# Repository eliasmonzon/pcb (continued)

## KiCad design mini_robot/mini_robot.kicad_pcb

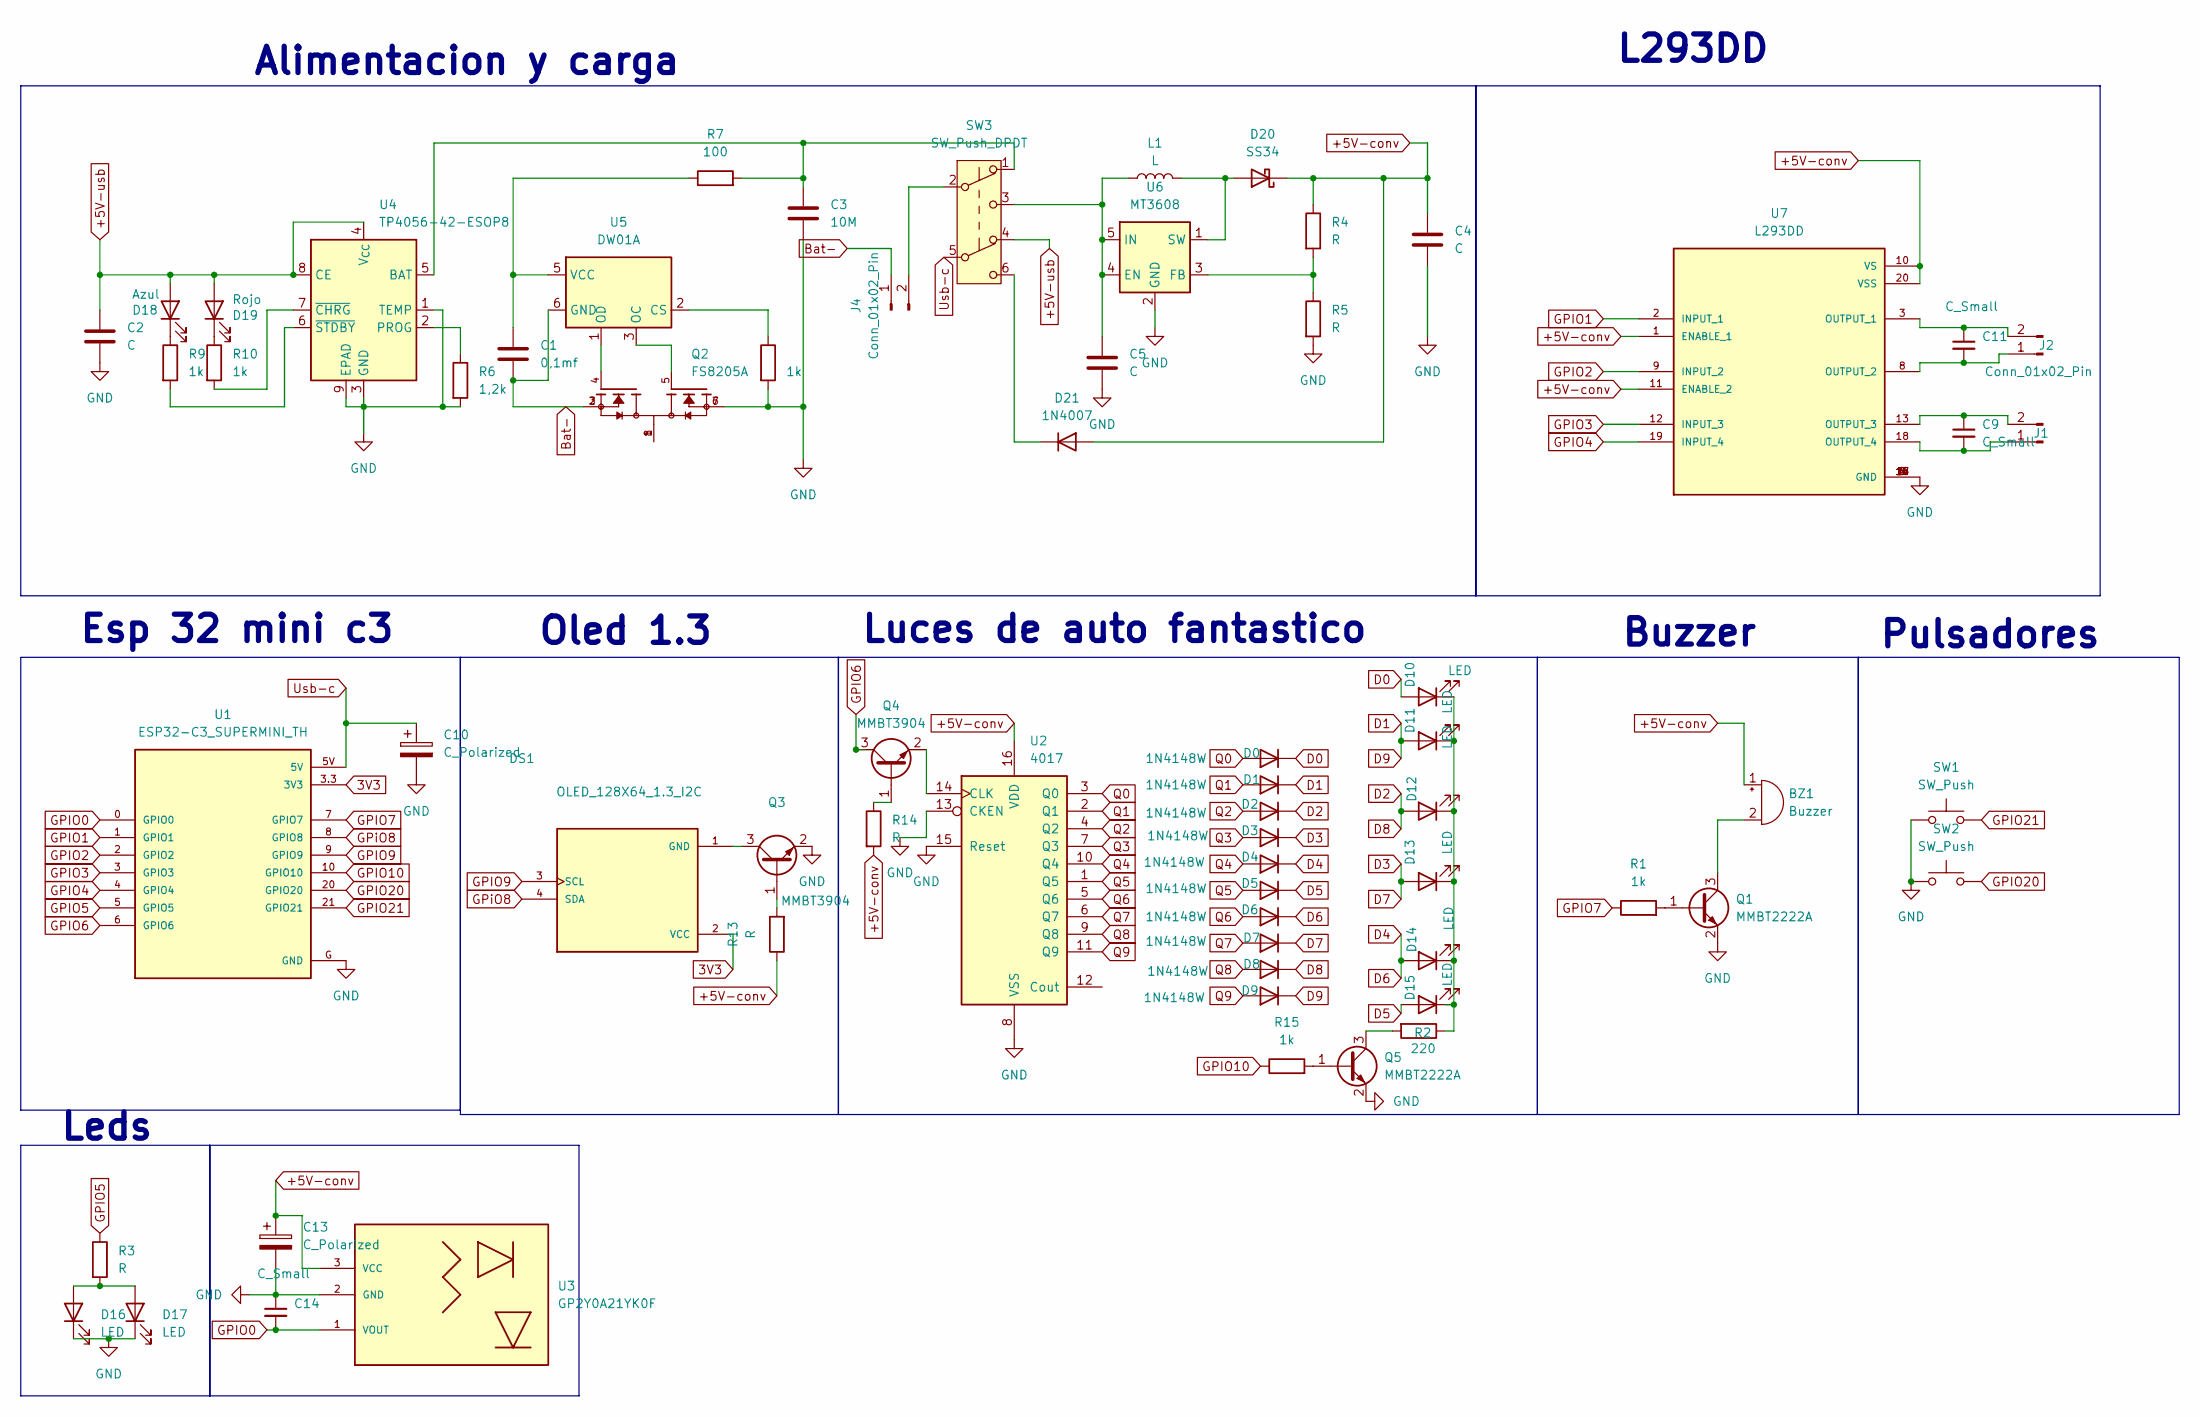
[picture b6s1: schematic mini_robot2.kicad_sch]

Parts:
BZ1: Buzzer; Buzzer_12x9.5RM7.6
C1: 0,1mf; C_1206_3216Metric
C2, C4, C5: C; C_1206_3216Metric
C3: 10M; C_1206_3216Metric
C9, C11, C14: C_Small; C_1206_3216Metric
C10, C13: C_Polarized; CP_Elec_3x5.3
D0, D1, D2, D3, D4, D5, D6, D7, D8, D9: 1N4148W; D_SOD-123
D10, D11, D12, D13, D14, D15, D16, D17: LED; LED_D5.0mm_Horizontal_O3.81mm_Z3.0mm
D18: Azul; LED_D3.0mm
D19: Rojo; LED_D3.0mm
D20: SS34; D_SMA
D21: 1N4007; D_1206_3216Metric_Pad1.42x1.75mm_HandSolder
DS1: OLED_128X64_1.3_I2C; LCD_OLED_128X64_1.3_I2C; PARTREV NA
J1, J2, J4: Conn_01x02_Pin; JST_EH_B2B-EH-A_1x02_P2.50mm_Vertical
L1: L; L_12x12mm_H8mm
Q1, Q5: MMBT2222A; SOT-23
Q2: FS8205A; SSO-8_6.8x5.9mm_P1.27mm_Clearance7mm; PARTREV 1.7
Q3, Q4: MMBT3904; SOT-23
R1, R8, R9, R10, R15: 1k; R_1206_3216Metric
R2: 220; R_1206_3216Metric
R3, R4, R5, R13, R14: R; R_1206_3216Metric
R6: 1,2k; R_1206_3216Metric
R7: 100; R_1206_3216Metric
SW1, SW2: SW_Push; SW_PUSH-12mm
SW3: SW_Push_DPDT; SW_E-Switch_EG2219_DPDT_Angled
U1: ESP32-C3_SUPERMINI_TH; MODULE_ESP32-C3_SUPERMINI_TH
U2: 4017; SOIC-16_3.9x9.9mm_P1.27mm
U3: GP2Y0A21YK0F; JST_EH_B3B-EH-A_1x03_P2.50mm_Vertical
U4: TP4056-42-ESOP8; SOIC-8-1EP_3.9x4.9mm_P1.27mm_EP2.41x3.3mm_ThermalVias
U5: DW01A; SOT-23-6
U6: MT3608; SOT-23-6
U7: L293DD; SOIC127P1032X265-20N; PARTREV N/A

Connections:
3V3: DS1.2 (VCC), U1.3.3 (3V3)
+5V-conv: BZ1.1 (+), C4.1, C13.1, D20.1 (K), D21.2 (A), R4.1, R13.1, R14.2, U2.16 (VDD), U3.3 (VCC), U7.1 (ENABLE_1), U7.10 (VS), U7.11 (ENABLE_2), U7.20 (VSS)
+5V-usb: C2.1, D18.2 (A), D19.2 (A), SW3.4 (A), U4.4 (V_{CC}), U4.8 (CE)
Bat-: C1.2, J4.1, Q2.2, Q2.3, U5.6 (GND)
D0: D0.1 (K), D10.2 (A)
D1: D1.1 (K), D9.1 (K), D11.2 (A)
D2: D2.1 (K), D8.1 (K), D12.2 (A)
D3: D3.1 (K), D7.1 (K), D13.2 (A)
D4: D4.1 (K), D6.1 (K), D14.2 (A)
D5: D5.1 (K), D15.2 (A)
GND: C2.2, C3.2, C4.2, C5.2, C10.2, C13.2, C14.1, D16.1 (K), D17.1 (K), Q1.2 (E), Q2.6, Q2.7, Q3.2 (E), Q5.2 (E), R5.2, R6.2, R8.2, SW1.1, SW2.1, U1.G (GND), U2.8 (VSS), U2.13 (CKEN), U2.15 (Reset), U3.2 (GND), U4.1 (TEMP), U4.3 (GND), U4.9 (EPAD), U6.2 (GND), U7.4 (GND), U7.5 (GND), U7.6 (GND), U7.7 (GND), U7.14 (GND), U7.15 (GND), U7.16 (GND), U7.17 (GND)
GPIO0: C14.2, U1.0 (GPIO0), U3.1 (VOUT)
GPIO1: U1.1 (GPIO1), U7.2 (INPUT_1)
GPIO2: U1.2 (GPIO2), U7.9 (INPUT_2)
GPIO3: U1.3 (GPIO3), U7.12 (INPUT_3)
GPIO4: U1.4 (GPIO4), U7.19 (INPUT_4)
GPIO5: R3.1, U1.5 (GPIO5)
GPIO6: Q4.3 (C), U1.6 (GPIO6)
GPIO7: R1.1, U1.7 (GPIO7)
GPIO9: DS1.3 (SCL), U1.9 (GPIO9)
GPIO10: R15.1, U1.10 (GPIO10)
GPIO20: SW2.2, U1.20 (GPIO20)
GPIO21: SW1.2, U1.21 (GPIO21)
GPiO8: DS1.4 (SDA), U1.8 (GPIO8)
unnamed: BZ1.2 (-), Q1.3 (C)
unnamed: D10.1 (K), D11.1 (K), D12.1 (K), D13.1 (K), D14.1 (K), D15.1 (K), R2.1
unnamed: D16.2 (A), D17.2 (A), R3.2
unnamed: D18.1 (K), R9.1
unnamed: D19.1 (K), R10.1
unnamed: D20.2 (A), L1.2, U6.1 (SW)
unnamed: D21.1 (K), SW3.6 (C)
unnamed: DS1.1 (GND), Q3.3 (C)
unnamed: C9.2, J1.1, U7.18 (OUTPUT_4)
unnamed: C9.1, J1.2, U7.13 (OUTPUT_3)
unnamed: C11.2, J2.1, U7.8 (OUTPUT_2)
unnamed: C11.1, J2.2, U7.3 (OUTPUT_1)
unnamed: J4.2, SW3.2 (B)
unnamed: Q1.1 (B), R1.2
unnamed: Q2.1, Q2.8
unnamed: Q3.1 (B), R13.2
unnamed: Q4.1 (B), R14.1
unnamed: Q4.2 (E), U2.14 (CLK)
unnamed: Q5.1 (B), R15.2
unnamed: Q5.3 (C), R2.2
unnamed: C3.1, R7.2, SW3.1 (A), U4.5 (BAT)
unnamed: R6.1, U4.2 (PROG)
unnamed: R10.2, U4.7 (~CHRG)
unnamed: R9.2, U4.6 (~STDBY)
unnamed: R8.1, U5.2 (CS)
unnamed: Q2.5, U5.3 (OC)
unnamed: Q2.4, U5.1 (OD)
unnamed: C1.1, R7.1, U5.5 (VCC)
unnamed: C5.1, L1.1, SW3.3 (C), U6.4 (EN), U6.5 (IN)
unnamed: R4.2, R5.1, U6.3 (FB)
Q0: D0.2 (A), U2.3 (Q0)
Q1: D1.2 (A), U2.2 (Q1)
Q2: D2.2 (A), U2.4 (Q2)
Q3: D3.2 (A), U2.7 (Q3)
Q4: D4.2 (A), U2.10 (Q4)
Q5: D5.2 (A), U2.1 (Q5)
Q6: D6.2 (A), U2.5 (Q6)
Q7: D7.2 (A), U2.6 (Q7)
Q8: D8.2 (A), U2.9 (Q8)
Q9: D9.2 (A), U2.11 (Q9)
Usb-c: C10.1, SW3.5 (B), U1.5V

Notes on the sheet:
Alimentacion y carga
Esp 32 mini c3
Oled 1.3
L293DD
Luces de auto fantastico
Pulsadores
Leds
Buzzer

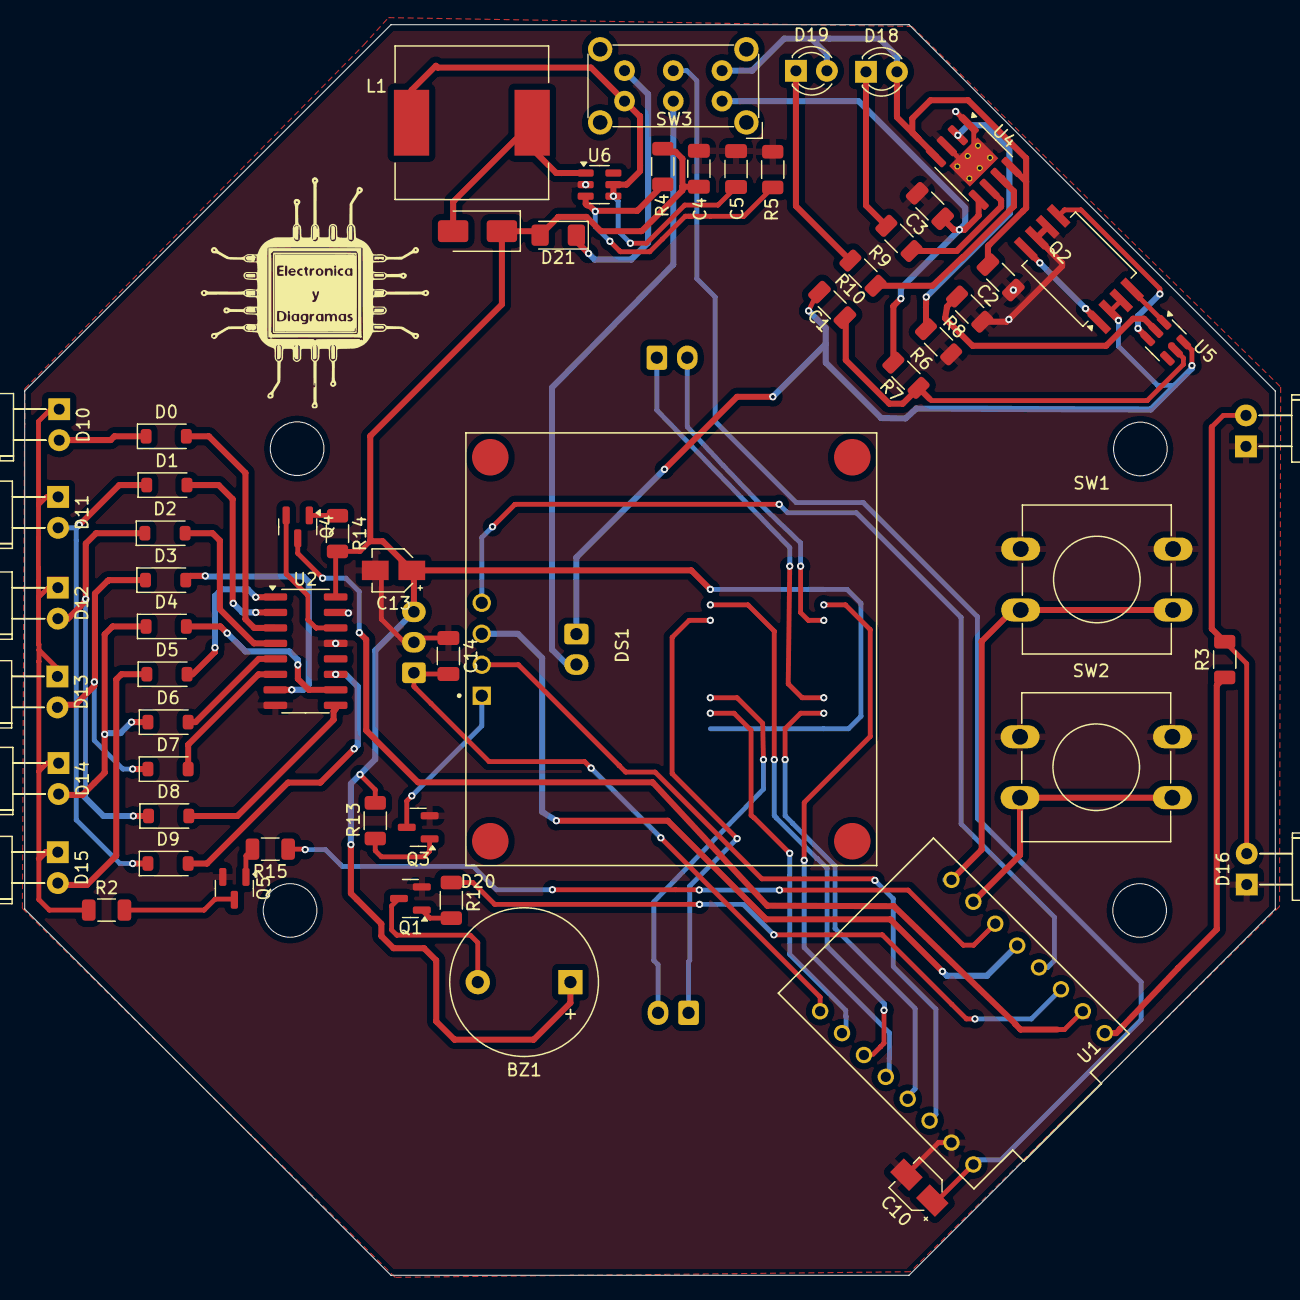
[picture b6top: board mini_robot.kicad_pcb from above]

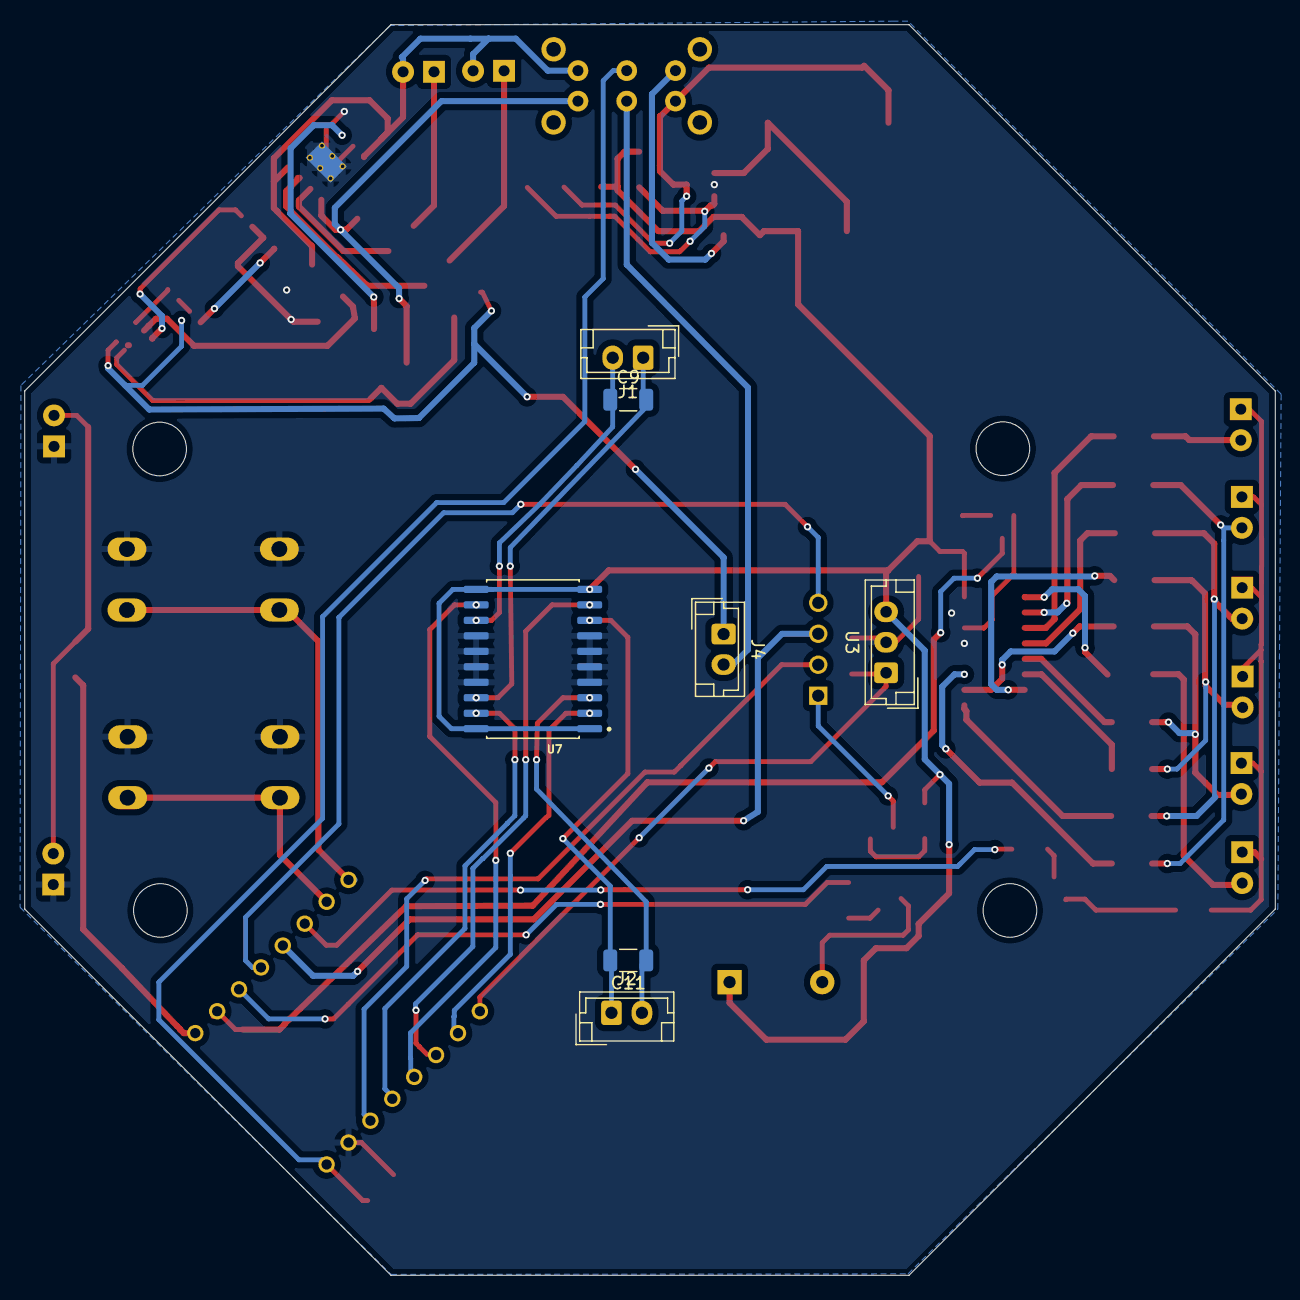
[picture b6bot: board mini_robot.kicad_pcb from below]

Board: 2 copper layers, 102.6 x 102.6 mm, 66 parts (7 on the bottom side), 65 nets.

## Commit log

2026-01-13 Subo archivos iniciales del proyecto PCB
